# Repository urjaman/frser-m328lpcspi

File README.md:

frser-m328lpcspi
================

Flashrom serprog device code for LPC/FWH + SPI on an atmega328p at 5V.

### Troubleshooting

Note that the flasher has a small interactive debug interface. This is
available on the serial terminal if a space character is sent.
Enter `?` to see available commands.

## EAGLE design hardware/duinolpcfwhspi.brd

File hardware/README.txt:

There was no schematic, it was done in EAGLE board editor,
but now i made a schematic just so you can see the connections...
Because apparently people cant read a board :| .
Also exported a schematic.png

The basic connections can be gleaned from flash.c
or with EAGLE and also the resistor values can be had from
eagle, but i'll write them here for faster reference

around SPI:
leftmost: CS pullup resistor 4k7
resistors near board top edge (above) 2k2
resistor below them 4k7

below PLCC32 socket:
leftmost 4: 2k2 pullup for data lines
next 2: 4k7 pullup for RST and INIT
next 4 (oriented left-right):
the ones near board edge (below) are 4k7
the ones above them are 2k2

The .zip contains the gerber files, or you 
can see:
https://oshpark.com/shared_projects/E6jwmbWy

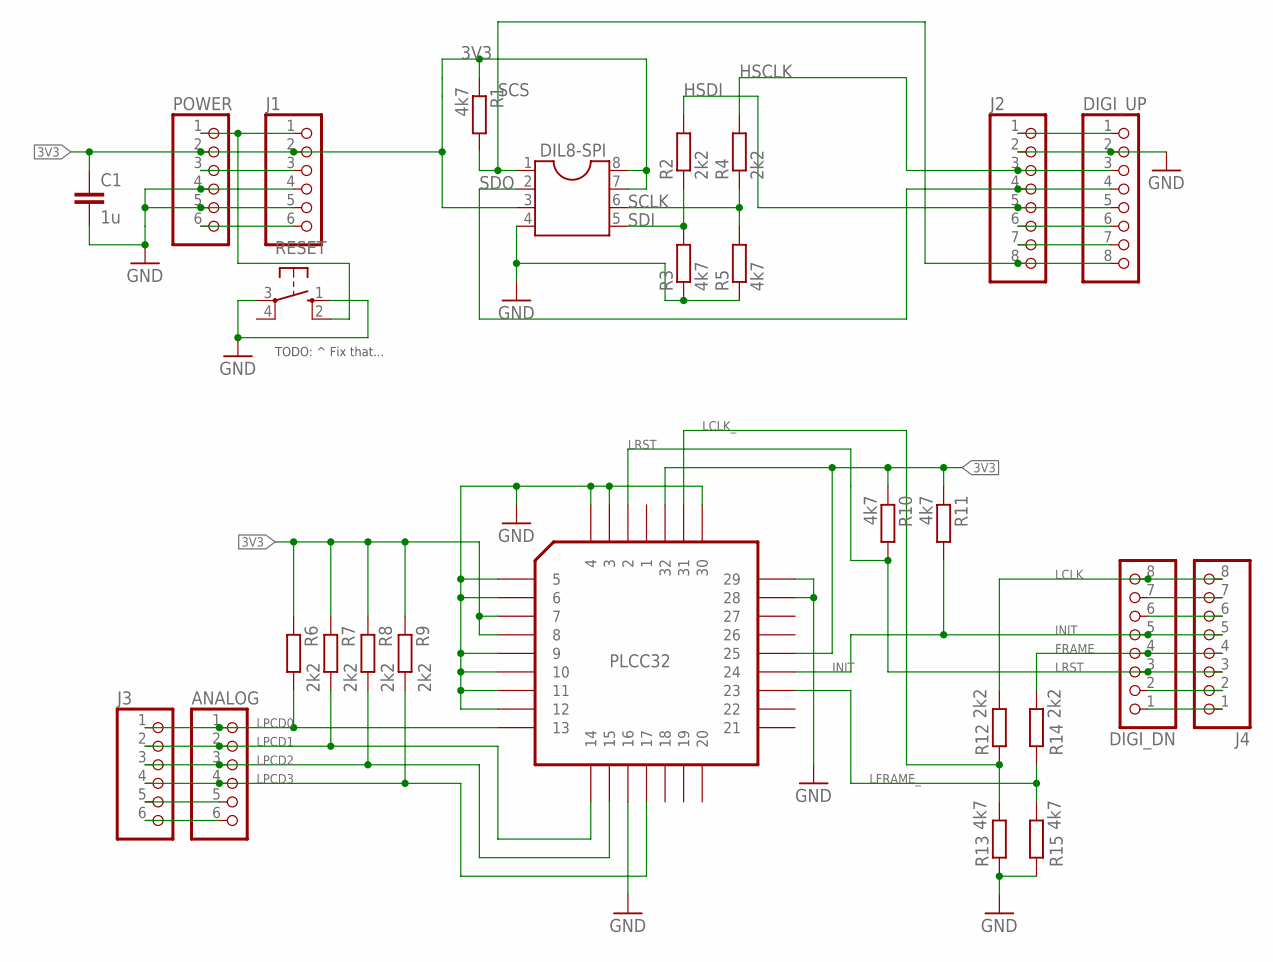
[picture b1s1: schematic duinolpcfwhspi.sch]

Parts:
ANALOG: PINHD-1X6; 1X06
C1: 1u; C025-025X050
DIGI_DN: PINHD-1X8TH; 1X08-TH
DIGI_UP: PINHD-1X8TH; 1X08-TH
DIL8-SPI: DIL8; DIL08
J1, J3: PINHD-1X6; 1X06
J2, J4: PINHD-1X8TH; 1X08-TH
PLCC32: PLCC32; PLCC-S32
POWER: PINHD-1X6; 1X06
R1, R3, R5, R10, R11, R13, R15: 4k7; 0207/2V
R2, R4, R6, R7, R8, R9, R12, R14: 2k2; 0207/2V
RESET: 10-XX; B3F-10XX

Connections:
3V3: C1.1, DIL8-SPI.3, DIL8-SPI.7, DIL8-SPI.8, J1.2, PLCC32.7, PLCC32.8, PLCC32.25, PLCC32.32, POWER.2, R1.1, R6.1, R7.1, R8.1, R9.1, R10.1, R11.1
5V0: J1.3, POWER.3
AREF: DIGI_UP.1, J2.1
FRAME: DIGI_DN.4, J4.4, R14.2
GND: C1.2, DIGI_UP.2, DIL8-SPI.4, J1.4, J1.5, J2.2, PLCC32.3, PLCC32.4, PLCC32.5, PLCC32.6, PLCC32.9, PLCC32.10, PLCC32.11, PLCC32.12, PLCC32.16, PLCC32.28, PLCC32.29, PLCC32.30, POWER.4, POWER.5, R3.1, R5.1, R13.1, R15.1, RESET.1 (S), RESET.3
HSCLK: DIGI_UP.3, J2.3, R4.2
HSDI: DIGI_UP.5, J2.5, R2.2
INIT: DIGI_DN.5, J4.5, PLCC32.24, R11.2
LCLK: DIGI_DN.8, J4.8, R12.2
LCLK_: PLCC32.31, R12.1, R13.2
LFRAME_: PLCC32.23, R14.1, R15.2
LPCD0: ANALOG.1, J3.1, PLCC32.13, R6.2
LPCD1: ANALOG.2, J3.2, PLCC32.14, R7.2
LPCD2: ANALOG.3, J3.3, PLCC32.15, R8.2
LPCD3: ANALOG.4, J3.4, PLCC32.17, R9.2
LRST: DIGI_DN.3, J4.3, PLCC32.2, R10.2
PB1: DIGI_UP.7, J2.7
PB2: DIGI_UP.6, J2.6
PC4: ANALOG.5, J3.5
PC5: ANALOG.6, J3.6
PD0: DIGI_DN.1, J4.1
PD1: DIGI_DN.2, J4.2
PD5: DIGI_DN.6, J4.6
PD6: DIGI_DN.7, J4.7
RESET: J1.1, POWER.1, RESET.2 (S1)
SCLK: DIL8-SPI.6, R4.1, R5.2
SCS: DIGI_UP.8, DIL8-SPI.1, J2.8, R1.2
SDI: DIL8-SPI.5, R2.1, R3.2
SDO: DIGI_UP.4, DIL8-SPI.2, J2.4
VIN: J1.6, POWER.6

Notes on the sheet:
TODO: ^ Fix that...

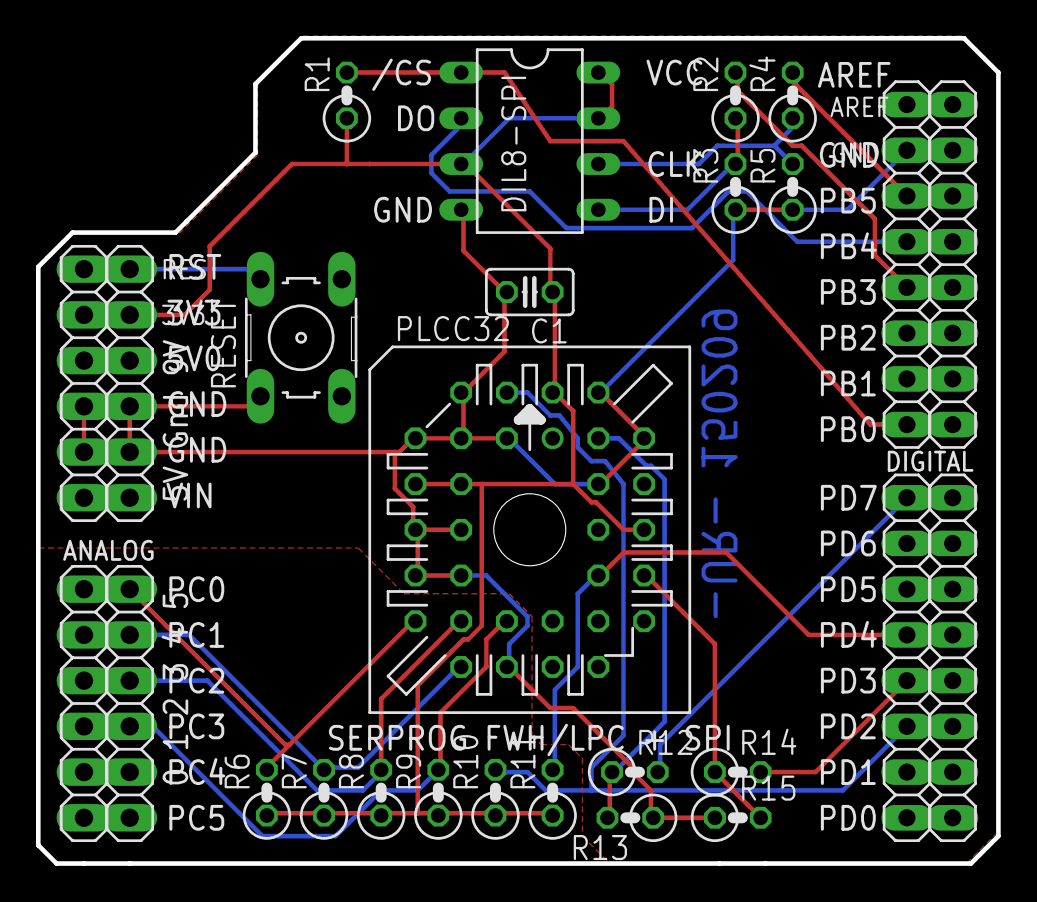
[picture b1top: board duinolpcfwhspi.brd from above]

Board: 2 copper layers, 53.3 x 45.8 mm, 27 parts (0 on the bottom side), 30 nets.

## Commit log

2015-03-08 Convert to M328 LPC/FWH + SPI firmware
2015-03-08 Include hardware (the board) description files
2015-03-09 Use libfrser :)
2015-03-09 change project name
2015-03-09 for really ...
2015-03-10 Enable -O3 (and fix one thing gcc found at -O3).
    This makes LPC go from read at 42 kB/s to 73 kB/s.
    And a full chip rewrite for 512k is ~4.5 min now.
    It also blows up the firmware size, but its not like we
    have any other use for it right now :)
2015-03-21 commands: optimize with -Os so we fit in 16k for mega168s
2015-03-21 modify flash.c to allow redefining LPC CLK to not PD7
2015-03-21 make uart buffer sizes auto-scale with RAM size so you dont need to mess with them
2015-03-23 DUH. That was stupid. Fix flash.c PORTB settings...
2015-03-23 spi: cleanup the speed-setting code a bit and re-arrange a bit
    in preparation of splitting hardware-dependent and independent
    parts out of each other
2015-03-23 use the spi support that was copied/moved into libfrser
2015-04-10 Update used libfrser
2015-04-10 lpc/fwh/nibble: small cleanup to prepare for libfrserization of them
2015-04-10 Use LPC & FWH code provided by libfrser
2015-04-10 Move with libfrser to a smaller nibble API
2015-04-25 hardware documentation: add schematic i just hacked together
2015-04-25 Use bugfixed libfrser
2015-05-23 uart: optimize ISR code for compiler to do a better job
    Results in 8 (my guesstimate) less cycles (2 less pushed regs)
    in the ISR, thus 10% more time for other stuff during RX at 2Mbps.
    Actually won 6s in flashing 512k LPC, but whatever.
2015-05-23 Makefile: allow overriding serial device from command line
2015-05-23 Use update libfrser
2015-05-23 nibble: allow gcc to optimize nibble writes better
    This way it can optimize out the complement (when we
    show it before the abstract asm swap) in half of
    the writes of the address writing routine.
2015-11-25 serprog-v2 version of m328lpcspi...
2015-11-25 dbg output help stuff
2022-04-19 Add a debugging command to test the LPC pins.
2023-02-25 add wiring voltage tests for spi pins
2023-02-25 Add mention of debug menu to README.
